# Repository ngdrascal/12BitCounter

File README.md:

# A configurable 12 Bit Configurable Counter

<Figure>
    
    <figcaption>Figure 1: Board top</figcaption>
</figure>

<Figure>
    
    <figcaption>Figure 2: Board bottom</figcaption>
</figure>

<Figure>
    
    <figcaption>Figure 3: Breadboard</figcaption>
</figure>

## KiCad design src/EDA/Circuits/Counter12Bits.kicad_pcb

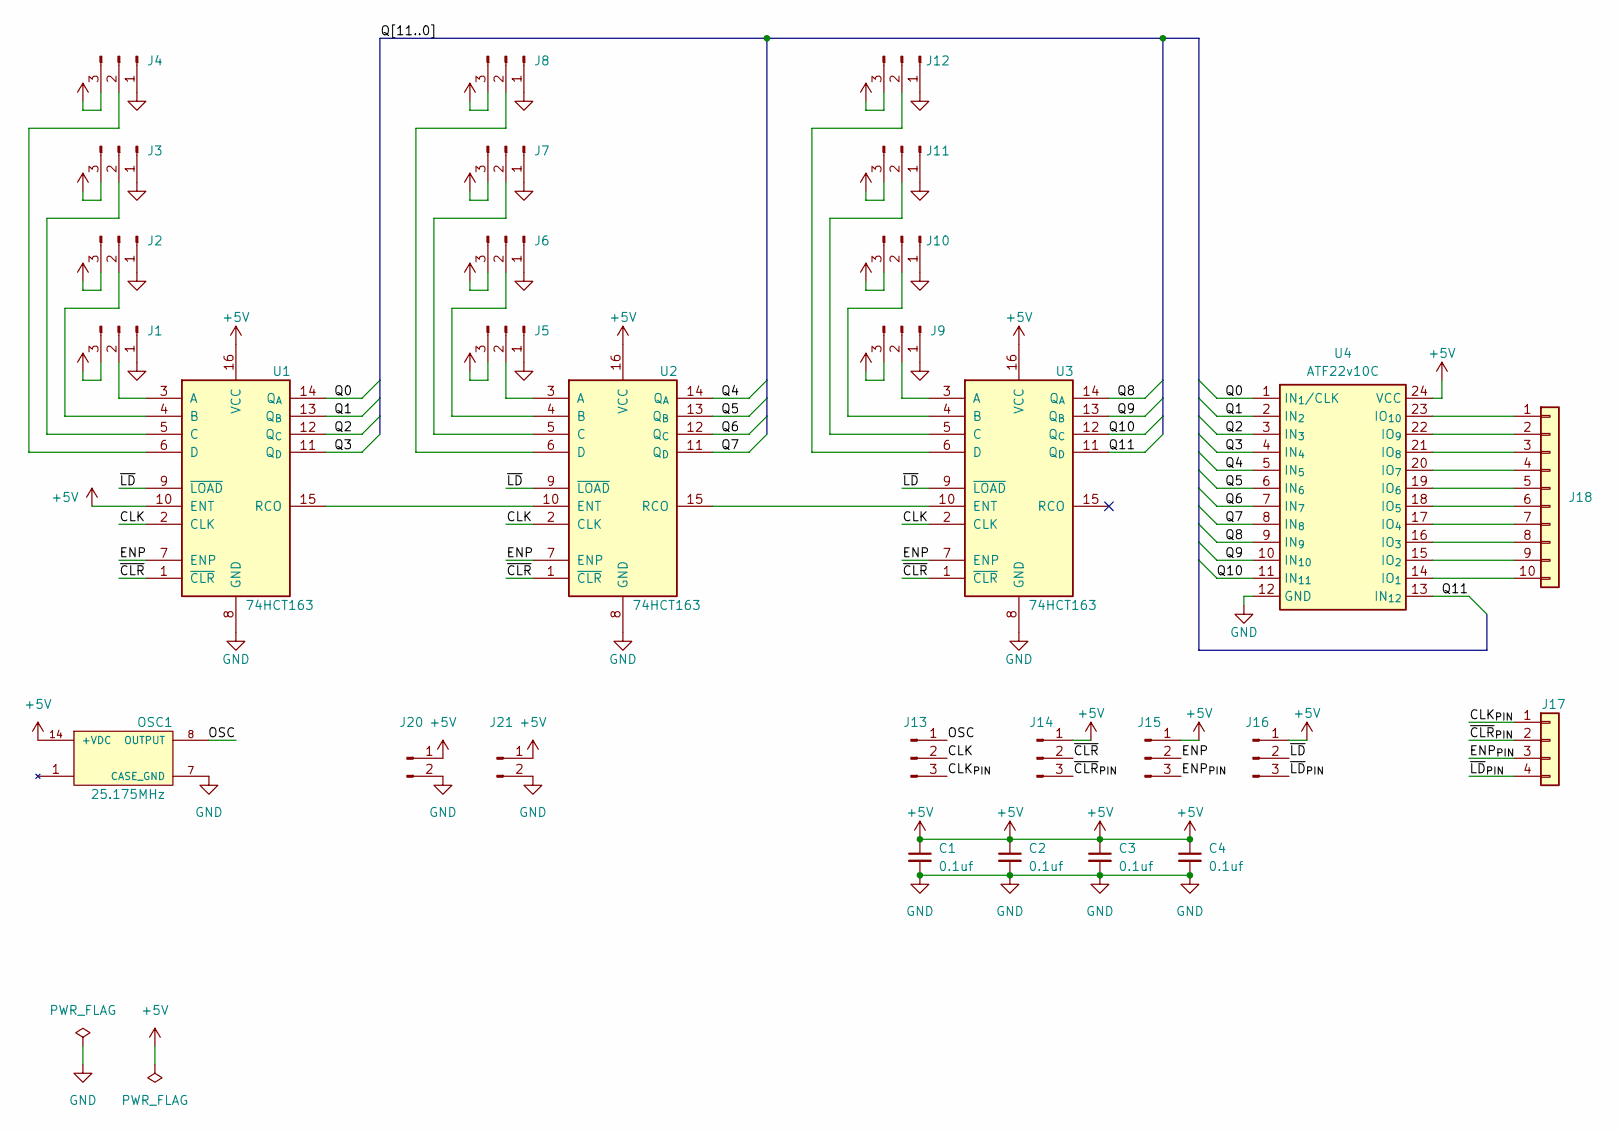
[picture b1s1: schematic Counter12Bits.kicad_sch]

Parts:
C1, C2, C3, C4: 0.1uf; C_Disc_D5.0mm_W2.5mm_P5.00mm
J1, J2, J3, J4, J5, J6, J7, J8, J9, J10, J11, J12, J13, J14, J15, J16: Conn_01x03_Pin; PinHeader_1x03_P2.54mm_Vertical
J17: Conn_01x04; PinHeader_1x04_P2.54mm_Vertical
J18: Conn_01x10; PinHeader_1x10_P2.54mm_Vertical
J20, J21: Conn_01x02_Pin; PinHeader_1x02_P2.54mm_Vertical
OSC1: 25.175MHz; OSC_ECS-100A-251.7
U1, U2, U3: 74HCT163; DIP-16_W7.62mm_LongPads
U4: ATF22v10C; DIP-24_W7.62mm_LongPads

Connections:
+5V: C1.1, C2.1, C3.1, C4.1, J1.3, J2.3, J3.3, J4.3, J5.3, J6.3, J7.3, J8.3, J9.3, J10.3, J11.3, J12.3, J14.1, J15.1, J16.1, J20.1, J21.1, OSC1.14 (+VDC), U1.10 (ENT), U1.16 (VCC), U2.16 (VCC), U3.16 (VCC), U4.24 (VCC)
/CLK: J13.2, U1.2 (CLK), U2.2 (CLK), U3.2 (CLK)
/CLK_{PIN}: J13.3, J17.1
/ENP: J15.2, U1.7 (ENP), U2.7 (ENP), U3.7 (ENP)
/ENP_{PIN}: J15.3, J17.3
/OSC: J13.1, OSC1.8 (OUTPUT)
/Q0: U1.14 (Q_{A}), U4.1 (IN_{1}/CLK)
/Q1: U1.13 (Q_{B}), U4.2 (IN_{2})
/Q2: U1.12 (Q_{C}), U4.3 (IN_{3})
/Q3: U1.11 (Q_{D}), U4.4 (IN_{4})
/Q4: U2.14 (Q_{A}), U4.5 (IN_{5})
/Q5: U2.13 (Q_{B}), U4.6 (IN_{6})
/Q6: U2.12 (Q_{C}), U4.7 (IN_{7})
/Q7: U2.11 (Q_{D}), U4.8 (IN_{8})
/Q8: U3.14 (Q_{A}), U4.9 (IN_{9})
/Q9: U3.13 (Q_{B}), U4.10 (IN_{10})
/Q10: U3.12 (Q_{C}), U4.11 (IN_{11})
/Q11: U3.11 (Q_{D}), U4.13 (IN_{12})
/~CLR: J14.2, U1.1 (~CLR), U2.1 (~CLR), U3.1 (~CLR)
/~CLR_{PIN}: J14.3, J17.2
/~LD: J16.2, U1.9 (~LOAD), U2.9 (~LOAD), U3.9 (~LOAD)
/~LD_{PIN}: J16.3, J17.4
GND: C1.2, C2.2, C3.2, C4.2, J1.1, J2.1, J3.1, J4.1, J5.1, J6.1, J7.1, J8.1, J9.1, J10.1, J11.1, J12.1, J20.2, J21.2, OSC1.7 (CASE_GND), U1.8 (GND), U2.8 (GND), U3.8 (GND), U4.12 (GND)
unnamed: J1.2, U1.3 (A)
unnamed: J2.2, U1.4 (B)
unnamed: J3.2, U1.5 (C)
unnamed: J4.2, U1.6 (D)
unnamed: J5.2, U2.3 (A)
unnamed: J6.2, U2.4 (B)
unnamed: J7.2, U2.5 (C)
unnamed: J8.2, U2.6 (D)
unnamed: J9.2, U3.3 (A)
unnamed: J10.2, U3.4 (B)
unnamed: J11.2, U3.5 (C)
unnamed: J12.2, U3.6 (D)
unnamed: J18.1, U4.23 (IO_{10})
unnamed: J18.2, U4.22 (IO_{9})
unnamed: J18.3, U4.21 (IO_{8})
unnamed: J18.4, U4.20 (IO_{7})
unnamed: J18.5, U4.19 (IO_{6})
unnamed: J18.6, U4.18 (IO_{5})
unnamed: J18.7, U4.17 (IO_{4})
unnamed: J18.8, U4.16 (IO_{3})
unnamed: J18.9, U4.15 (IO_{2})
unnamed: J18.10, U4.14 (IO_{1})
unnamed: U1.15 (RCO), U2.10 (ENT)
unnamed: U2.15 (RCO), U3.10 (ENT)

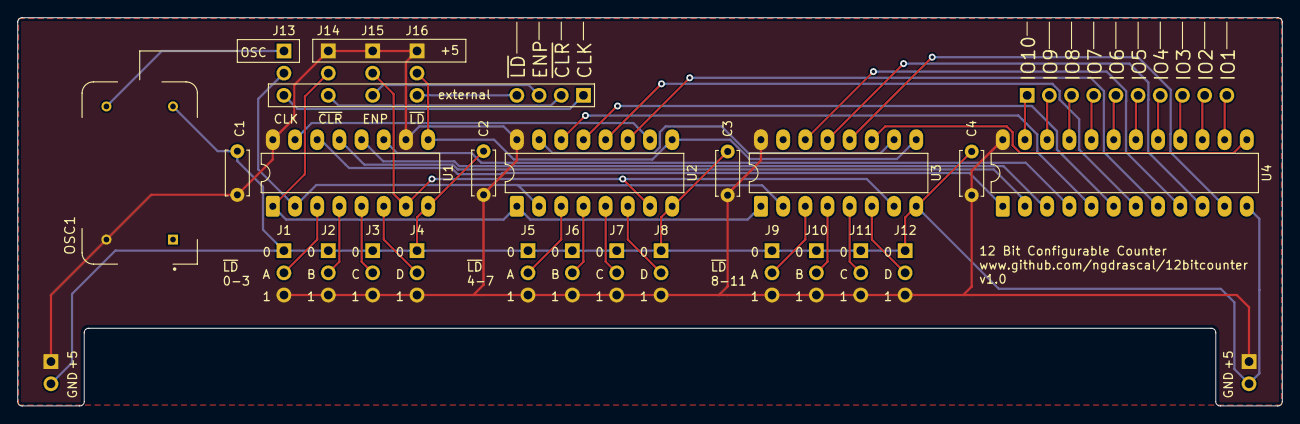
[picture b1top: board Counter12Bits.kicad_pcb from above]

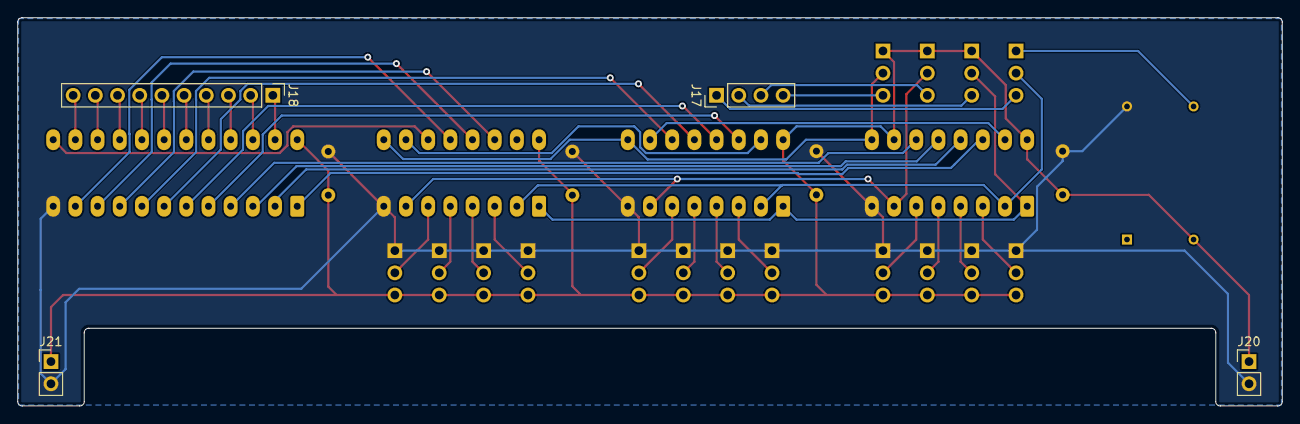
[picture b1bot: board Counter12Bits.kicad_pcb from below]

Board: 2 copper layers, 144.8 x 44.4 mm, 29 parts (4 on the bottom side), 47 nets.

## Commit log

2026-06-20 change pin name to match KiCad schematic
2026-06-20 add more tests
2026-06-21 change pin lable from LOAD to LD
2026-06-22 remove
